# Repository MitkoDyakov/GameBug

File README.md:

# GameBug
Open Hardware gaming pads for breadboard. 

Each pad features:
* 1 x analog X Y joystics from Adafruit
* 4 x 1.96N OMRON push buttons
* 1 shoulder button
* RGB LED for backlight
* Haptic feedback Maxim Integrated PWM controled vibrator motor driver + motor
* All buttons are debounced using a Texas Instruments schmitt trigger IC to eliminate glitches. 
* 2 x selector switches from Alpine 

It has 2.54 pitch headers for dropping directly into a breadboard. It is powered by 5V or 3.3V.

Great for teaching childer about electronics by bilding their own games.

Suitable for creating your own portable games or HID Joystic devices. 

Can be used to control CNC machines or for DIY RC projects.

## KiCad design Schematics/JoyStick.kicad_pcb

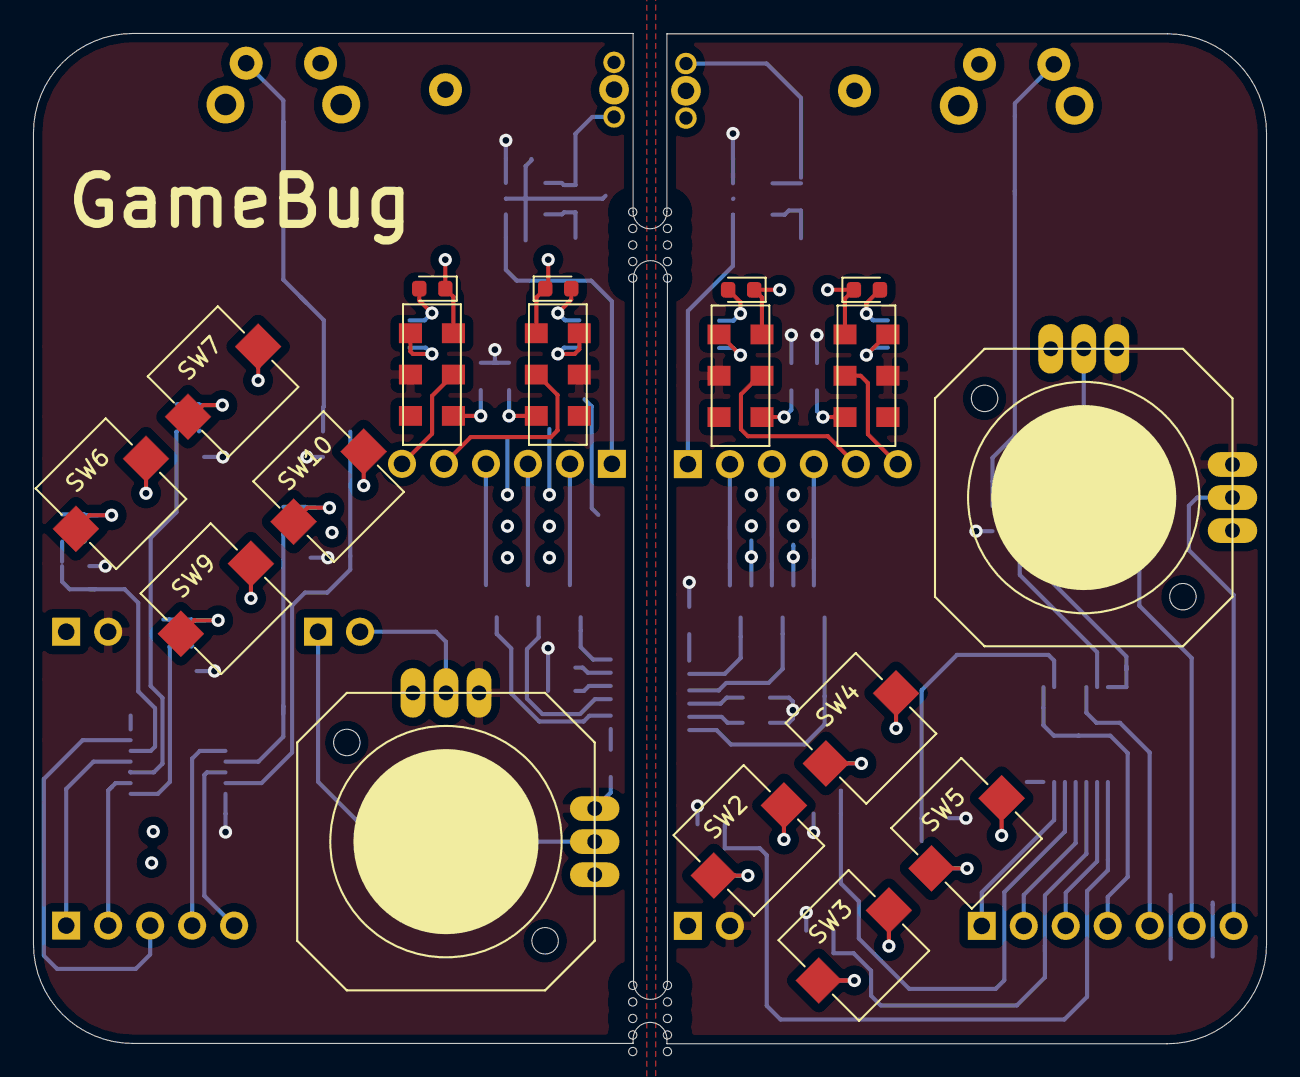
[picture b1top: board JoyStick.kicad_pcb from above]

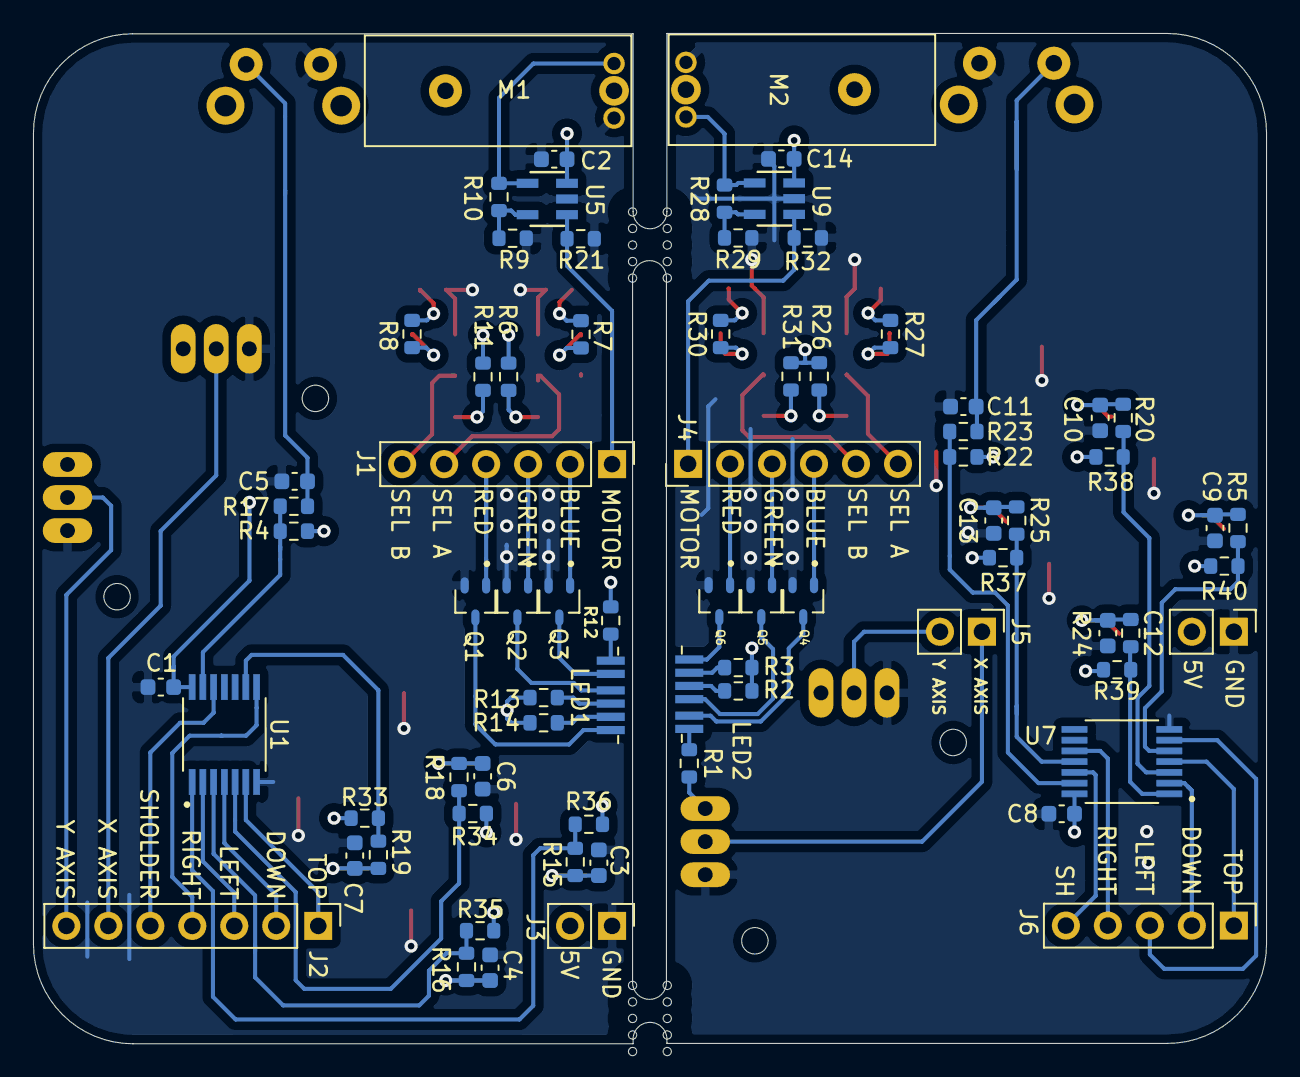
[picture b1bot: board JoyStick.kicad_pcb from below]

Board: 4 copper layers, 74.6 x 61.1 mm, 95 parts (75 on the bottom side), 77 nets.

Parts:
C1, C2, C3, C4, C5, C6, C7, C8, C9, C10, C11, C12, C13, C14: 100nF; C_0603_1608Metric
D1, D2, D3, D4: LED; LED_0603_1608Metric
J1, J4: Conn_01x06; PinHeader_1x06_P2.54mm_Vertical
J2: Conn_01x07; PinHeader_1x07_P2.54mm_Vertical
J3, J5, J7: Conn_01x02; PinHeader_1x02_P2.54mm_Vertical
J6: Conn_01x05; PinHeader_1x05_P2.54mm_Vertical
LED1, LED2: RGB; AELPS1.32
M1, M2: Motor_DC; 306-114_motor
Q1, Q2, Q3, Q4, Q5, Q6: NPN; SOT65P210X110-3N
R1, R2, R3, R4, R5, R6, R7, R8, R9, R10, R11, R12, R13, R14, R15, R16, R17, R18, R19, R20, R21, R22, R23, R24, R25, R26, R27, R28, R29, R30, R31, R32, R33, R34, R35, R36, R37, R38, R39, R40: R_Small; R_0603_1608Metric
SW1, SW8: SW_Push; 1825968-2
SW2, SW3, SW4, SW5, SW6, SW7, SW9, SW10: SW_Push; b3al-1000p
U1: U1; SOP65P640X120-14N
U2, U6: AnalogJoyStick; JOYSTICK_ANALOG_MINITHM
U3, U4, U8, U10: positionSwitch; CL-SB-22A-01
U5, U9: MAX; 21-0057F
U7: U7; SOP65P640X120-14N

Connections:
5V: C1.1, C2.1, J3.2, R4.2, R6.2, R11.2, R12.2, R13.2, R14.2, R33.1, R34.1, R35.1, R36.1, U1.14, U2.3, U2.6, U3.5, U4.2, U5.3
5V_2: C8.1, C14.1, J7.2, R1.2, R2.2, R3.2, R22.2, R26.2, R31.2, R37.1, R38.1, R39.1, R40.1, U6.3, U6.6, U7.14, U8.5, U9.3, U10.2
BLUE_LED: J1.2, Q3.1
BLUE_LED_2: J4.4, Q4.1
B_TR: LED1.5, Q3.3
B_TR_2: LED2.5, Q4.3
DOWN: R16.1, R35.2, U1.3
DOWN_2: R24.1, R39.2, U7.1
GND: C1.2, C2.2, C3.2, C4.2, C5.2, C6.2, C7.2, C8.2, C9.2, C10.2, C11.2, C12.2, C13.2, C14.2, D1.1, D2.1, D3.1, D4.1, J3.1, J7.1, M1.2, M2.2, Q1.2, Q2.2, Q3.2, Q4.2, Q5.2, Q6.2, R9.2, R21.1, R29.2, R32.1, SW1.2, SW2.2, SW3.2, SW4.2, SW5.2, SW6.2, SW7.2, SW8.1, SW9.2, SW10.2, U1.7, U2.1, U2.4, U3.3, U4.6, U5.2, U6.1, U6.4, U7.7, U8.3, U9.2, U10.6
GREEN_LED: J1.3, Q2.1
GREEN_LED_2: J4.3, Q5.1
G_TR: LED1.4, Q2.3
G_TR_2: LED2.4, Q5.3
LEFT: R15.1, R36.2, U1.1
LEFT_2: R5.1, R40.2, U7.5
MOTOR_PWM: J1.1, R21.2, U5.1
MOTOR_PWM_2: J4.1, R32.2, U9.1
unnamed: C3.1, R15.2, SW2.1
unnamed: C4.1, R16.2, SW3.1
unnamed: C5.1, R17.2, SW1.1
unnamed: C6.1, R18.2, SW4.1
unnamed: C7.1, R19.2, SW5.1
unnamed: C9.1, R5.2, SW6.1
unnamed: C10.1, R20.2, SW7.1
unnamed: C11.1, R23.2, SW8.2
unnamed: C12.1, R24.2, SW9.1
unnamed: C13.1, R25.2, SW10.1
unnamed: D1.2, R27.1
unnamed: D2.2, R30.2
unnamed: D3.2, R7.1
unnamed: D4.2, R8.2
unnamed: LED1.2, R14.1
unnamed: LED1.3, R13.1
unnamed: LED1.6, R12.1
unnamed: LED2.2, R3.1
unnamed: LED2.3, R2.1
unnamed: LED2.6, R1.1
unnamed: M1.1, R10.1, U5.4
unnamed: M2.1, R28.1, U9.4
unnamed: R6.1, U3.1
unnamed: R7.2, U3.6
unnamed: R8.1, U4.3
unnamed: R9.1, R10.2, U5.5
unnamed: R11.1, U4.4
unnamed: R26.1, U8.1
unnamed: R27.2, U8.6
unnamed: R28.2, R29.1, U9.5
unnamed: R30.1, U10.3
unnamed: R31.1, U10.4
RED_LED: J1.4, Q1.1
RED_LED_2: J4.2, Q6.1
RIGHT: R19.1, R33.2, U1.9
RIGHT_2: R25.1, R37.2, U7.11
R_TR: LED1.1, Q1.3
R_TR_2: LED2.1, Q6.3
SELECTOR_A: J1.5, U3.2
SELECTOR_A_2: J4.6, U8.2
SELECTOR_B: J1.6, U4.5
SELECTOR_B_2: J4.5, U10.5
SHOWDER_A: R4.1, R17.1, U1.13
SHOWDER_A_2: R22.1, R23.1, U7.13
TOP: R18.1, R34.2, U1.5
TOP_2: R20.1, R38.2, U7.3
X_Axis: J2.6, U2.2
X_Axis_2: J5.2, U6.2
Y_Axis: J2.7, U2.5
Y_Axis_2: J5.1, U6.5
cSHOWDER_A: J2.5, U1.12
cSHOWDER_A_2: J6.5, U7.12
dDOWN: J2.2, U1.4
dDOWN_2: J6.2, U7.2
dLEFT: J2.3, U1.2
dLEFT_2: J6.3, U7.6
dRIGHT: J2.4, U1.8
dRIGHT_2: J6.4, U7.10
dTOP: J2.1, U1.6
dTOP_2: J6.1, U7.4

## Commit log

2022-01-03 UpdateDatasheets
    add all datasheets
2022-01-03 cads
    cad models
2022-01-03 Update JoyStick.step
    Added shoulder buttons
2022-01-03 Create HID_JoyStick.ino
    Software Example
2022-01-03 Man files
    PCB bom and component placement
2022-01-03 Examples
    Empty Sceleton
2022-01-24 add test sketch
    Add test sketch to check functionality of the pads
2022-01-24 fix for motor pull down
2022-01-24 fix for motor pull down
    fix for
2022-01-24 add OSHW certificate
2022-01-25 Update Console.ino
    Xbox controller demo
